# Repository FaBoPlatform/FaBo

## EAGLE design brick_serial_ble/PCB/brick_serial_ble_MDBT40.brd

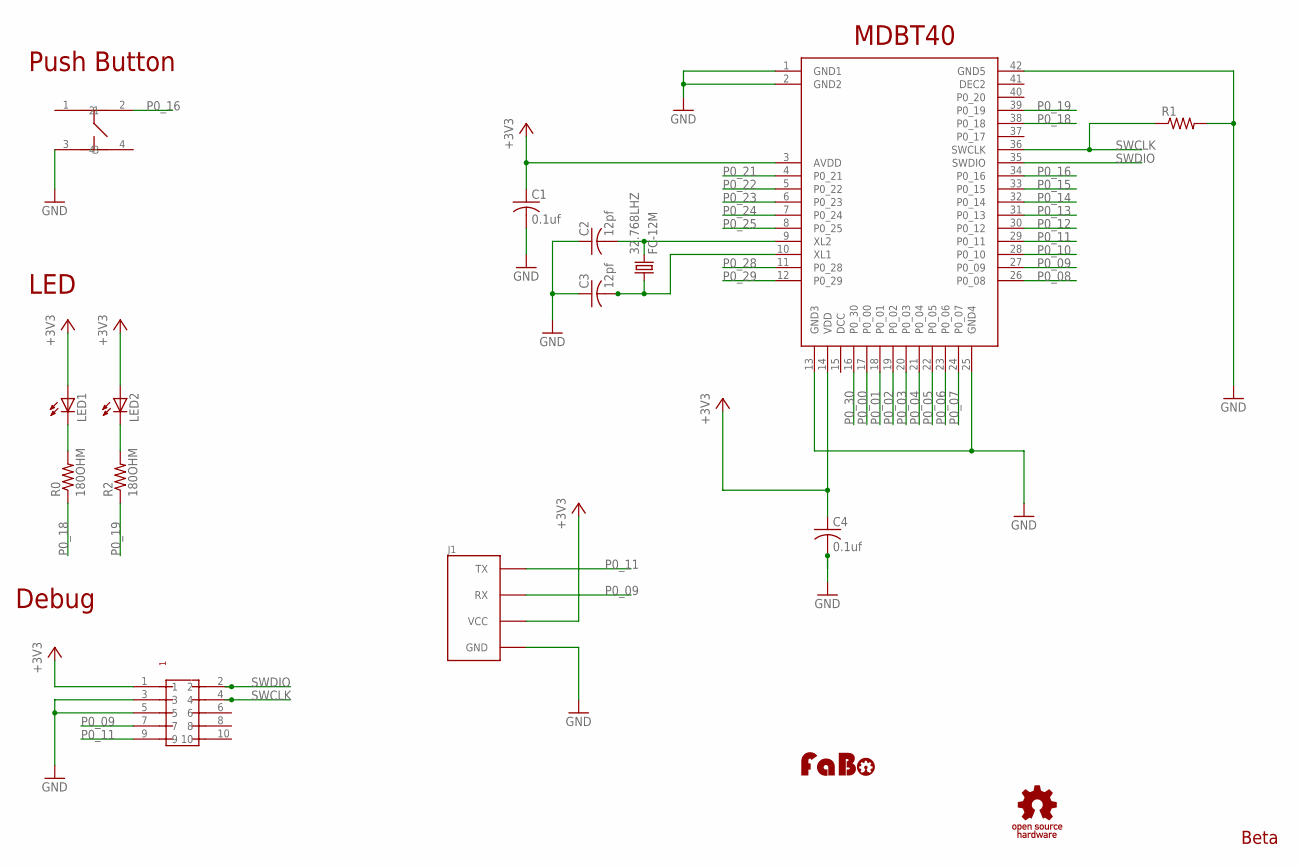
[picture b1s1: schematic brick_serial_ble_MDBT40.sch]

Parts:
32.768LHZ: FC-12M
C1, C4: 0.1uf; C0603
C2, C3: 12pf; C0603
J1: BRICK_SERIAL
LED1, LED2: LEDCHIP-LED0603; CHIP-LED0603
R0, R2: 180OHM; 0603-RES
R1: R-US_R0603; R0603
U$1: RAYTAC-MDBT40
U$2: PIN-HEADER-SMT(1.27MM)2X5
U$3: LOGO_FABO-S; LOGO_FABO_S
U$4: LOGO_OSHW_T-S; LOGO_OSHW_T_S
U$5: SWICTH-4P(KMR2); SWITCH-4P(KMR2)

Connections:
+3V3: C1.1, C4.1, J1.VCC, LED1.A, LED2.A, U$1.3 (AVDD), U$1.14 (VDD), U$2.1
GND: C1.2, C2.1, C3.1, C4.2, J1.GND, R1.2, U$1.1 (GND1), U$1.2 (GND2), U$1.13 (GND3), U$1.25 (GND4), U$1.42 (GND5), U$2.3, U$2.5, U$5.3
LED1: LED1.C, R0.2
unnamed: LED2.C, R2.2
unnamed: 32.768LHZ.2, C2.2, U$1.9 (XL2)
unnamed: 32.768LHZ.1, C3.2, U$1.10 (XL1)
P0_00: U$1.17 (P0_00)
P0_01: U$1.18 (P0_01)
P0_02: U$1.19 (P0_02)
P0_03: U$1.20 (P0_03)
P0_04: U$1.21 (P0_04)
P0_05: U$1.22 (P0_05)
P0_06: U$1.23 (P0_06)
P0_07: U$1.24 (P0_07)
P0_08: U$1.26 (P0_08)
P0_09: J1.RX, U$1.27 (P0_09), U$2.7
P0_10: U$1.28 (P0_10)
P0_11: J1.TX, U$1.29 (P0_11), U$2.9
P0_12: U$1.30 (P0_12)
P0_13: U$1.31 (P0_13)
P0_14: U$1.32 (P0_14)
P0_15: U$1.33 (P0_15)
P0_16: U$1.34 (P0_16), U$5.2
P0_18: R0.1, U$1.38 (P0_18)
P0_19: R2.1, U$1.39 (P0_19)
P0_21: U$1.4 (P0_21)
P0_22: U$1.5 (P0_22)
P0_23: U$1.6 (P0_23)
P0_24: U$1.7 (P0_24)
P0_25: U$1.8 (P0_25)
P0_28: U$1.11 (P0_28)
P0_29: U$1.12 (P0_29)
P0_30: U$1.16 (P0_30)
SWCLK: R1.1, U$1.36 (SWCLK), U$2.4
SWDIO: U$1.35 (SWDIO), U$2.2

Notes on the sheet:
Push Button
Debug
MDBT40
LED
Beta

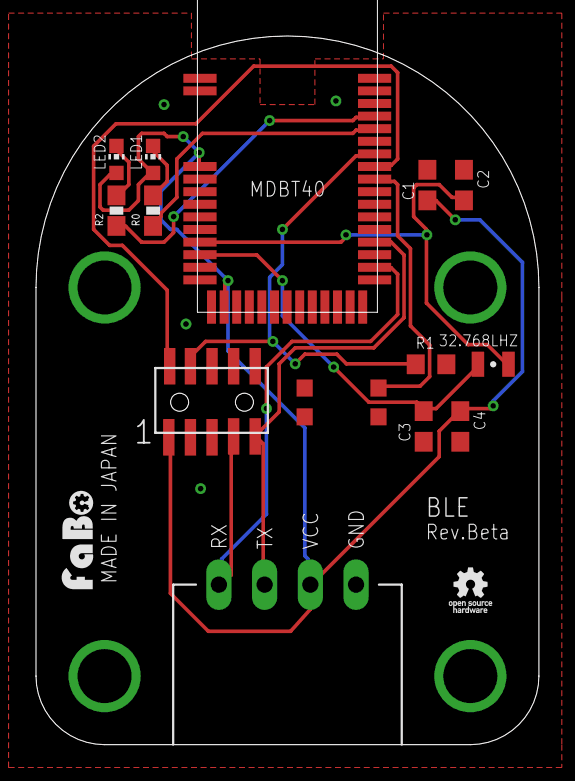
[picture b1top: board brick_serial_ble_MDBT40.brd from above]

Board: 2 copper layers, 27.9 x 39.4 mm, 16 parts (0 on the bottom side), 13 nets.

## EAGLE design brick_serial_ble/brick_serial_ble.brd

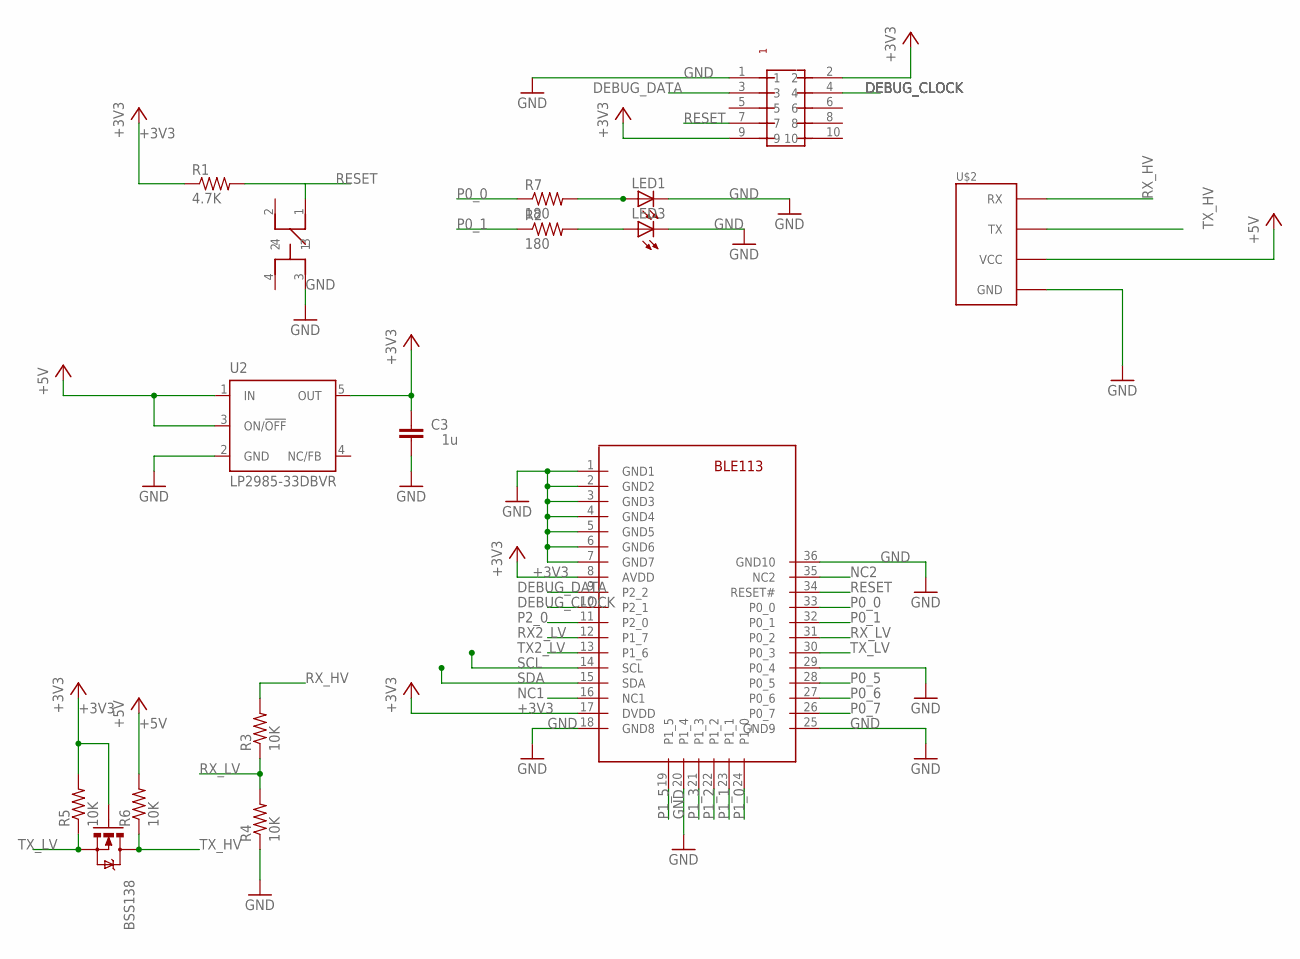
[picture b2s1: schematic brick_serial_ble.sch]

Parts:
BSS138: MOSFET-NCHANNELSMD; SOT23-3
C3: 1u; C0603-ROUND
LED1, LED3: LED_ESML0603; LED_SML0603
R1: 4.7K; 0603-RES
R2, R7: 180; 0603-RES
R3, R4, R5, R6: 10K; 0603-RES
U2: LP2985-33DBVR; SOT23-DBV
U$1: PIN-HEADER-SMT(1.27MM)2X5
U$2: BRICK_SERIAL
U$4: SWITCH-LS6J2M-T; SWICTH-LS6J2M-T
U$6: BLUEGIGA-BLE113

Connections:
+3V3: BSS138.1 (G), C3.2, R1.1, R5.2, U2.5 (OUT), U$1.2, U$1.9, U$6.8 (AVDD), U$6.17 (DVDD)
+5V: R6.2, U2.1 (IN), U2.3 (ON/!OFF), U$2.VCC
DEBUG_CLOCK: U$1.4, U$6.10 (P2_1)
DEBUG_DATA: U$1.3, U$6.9 (P2_2)
GND: C3.1, LED1.C, LED3.C, R4.1, U2.2 (GND), U$1.1, U$2.GND, U$4.3, U$6.1 (GND1), U$6.2 (GND2), U$6.3 (GND3), U$6.4 (GND4), U$6.5 (GND5), U$6.6 (GND6), U$6.7 (GND7), U$6.18 (GND8), U$6.20 (P1_4), U$6.25 (GND9), U$6.29 (P0_4), U$6.36 (GND10)
unnamed: LED1.A, R7.2
unnamed: LED3.A, R2.2
NC1: U$6.16 (NC1)
NC2: U$6.35 (NC2)
P0_0: R7.1, U$6.33 (P0_0)
P0_1: R2.1, U$6.32 (P0_1)
P0_5: U$6.28 (P0_5)
P0_6: U$6.27 (P0_6)
P0_7: U$6.26 (P0_7)
P1_0: U$6.24 (P1_0)
P1_1: U$6.23 (P1_1)
P1_2: U$6.22 (P1_2)
P1_3: U$6.21 (P1_3)
P1_5: U$6.19 (P1_5)
P2_0: U$6.11 (P2_0)
RESET: R1.2, U$1.7, U$4.1, U$6.34 (RESET#)
RX2_LV: U$6.12 (P1_7)
RX_HV: R3.2, U$2.RX
RX_LV: R3.1, R4.2, U$6.31 (P0_2)
SCL: U$6.14 (SCL)
SDA: U$6.15 (SDA)
TX2_LV: U$6.13 (P1_6)
TX_HV: BSS138.3 (D), R6.1, U$2.TX
TX_LV: BSS138.2 (S), R5.1, U$6.30 (P0_3)

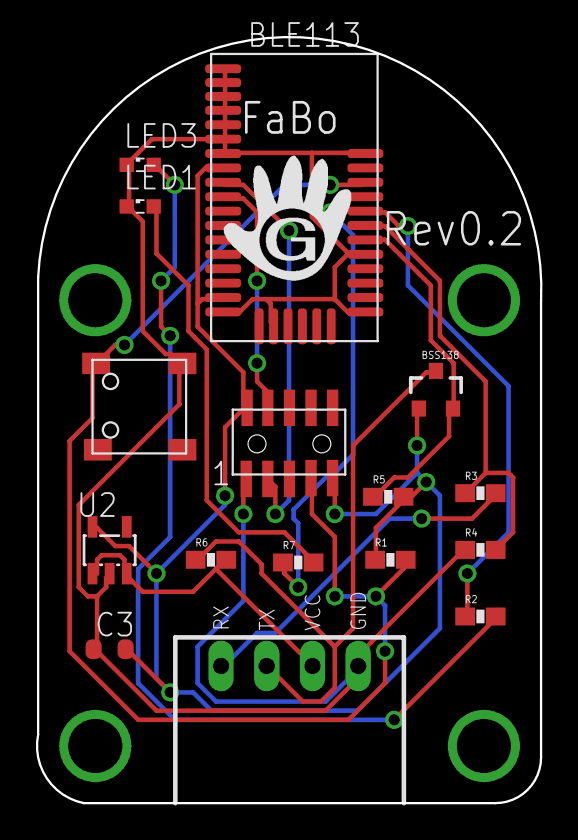
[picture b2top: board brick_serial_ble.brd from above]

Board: 2 copper layers, 28.0 x 42.6 mm, 16 parts (0 on the bottom side), 14 nets.

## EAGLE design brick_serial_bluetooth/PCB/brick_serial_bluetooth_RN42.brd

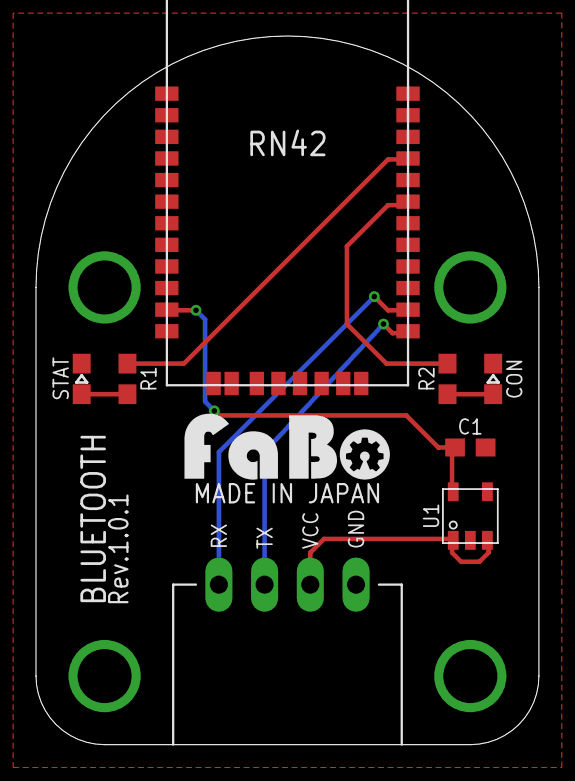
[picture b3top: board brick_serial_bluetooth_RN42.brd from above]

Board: 2 copper layers, 27.9 x 39.4 mm, 10 parts (0 on the bottom side), 9 nets.

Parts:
C1: 1uF; EIA0603
CON: EIA0603-LED
J1: FABO_BRICK_SERIAL
R1, R2: 220; EIA0603
STAT: EIA0603-LED
U1: SOT_23_5
U$1: MICROCHIP-RN42
U$3: LOGO_FABO_M
U$4: LOGO_OSHW_T_M_BOTTOM

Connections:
3V3: C1.1, U1.5, U$1.11
GND: C1.2, CON.C, J1.GND, STAT.C, U1.2, U$1.1, U$1.4, U$1.12, U$1.28, U$1.29
unnamed: R1.1, STAT.A
unnamed: R2.2, U$1.19
unnamed: R1.2, U$1.21
unnamed: CON.A, R2.1
unnamed: J1.VCC, U1.1, U1.3
RX: J1.RX, U$1.14
TX: J1.TX, U$1.13

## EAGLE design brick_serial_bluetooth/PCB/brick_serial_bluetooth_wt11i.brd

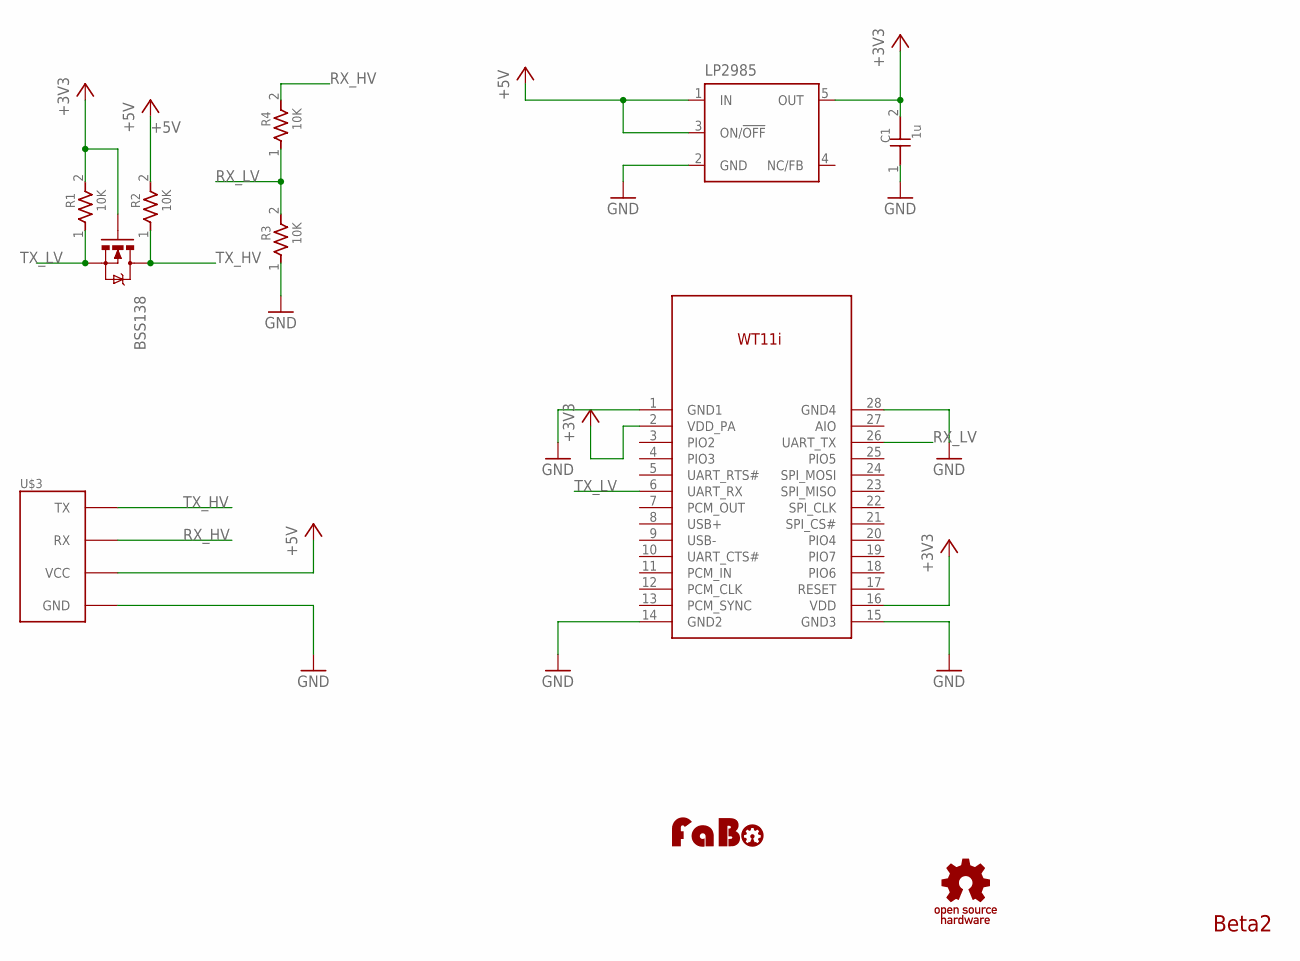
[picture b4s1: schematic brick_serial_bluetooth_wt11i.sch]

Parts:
BSS138: MOSFET-NCHANNELSMD; SOT23-3
C1: 1u; 0603
LP2985: LP2985-XXDBVR33; SOT23-DBV
R1, R2, R3, R4: 10K; 0603
U$1: BLUEGIGA-WT11I
U$3: BRICK_SERIAL
U$4: LOGO_OSHW_T-S; LOGO_OSHW_T_S
U$5: LOGO_FABO-S; LOGO_FABO_S

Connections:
+3V3: BSS138.1 (G), C1.2, LP2985.5 (OUT), R1.2, U$1.2 (VDD_PA), U$1.16 (VDD)
+5V: LP2985.1 (IN), LP2985.3 (ON/!OFF), R2.2, U$3.VCC
GND: C1.1, LP2985.2 (GND), R3.1, U$1.1 (GND1), U$1.14 (GND2), U$1.15 (GND3), U$1.28 (GND4), U$3.GND
RX_HV: R4.2, U$3.RX
RX_LV: R3.2, R4.1, U$1.26 (UART_TX)
TX_HV: BSS138.3 (D), R2.1, U$3.TX
TX_LV: BSS138.2 (S), R1.1, U$1.6 (UART_RX)

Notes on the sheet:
Beta2

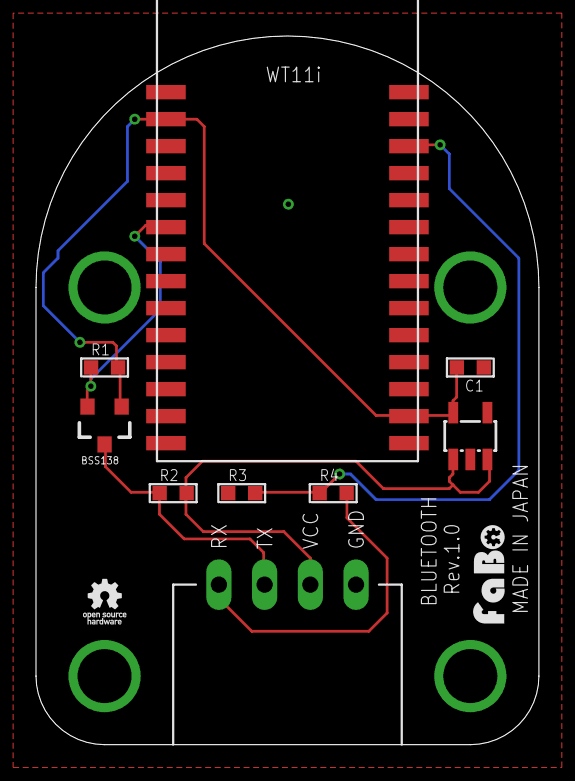
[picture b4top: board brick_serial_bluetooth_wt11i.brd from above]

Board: 2 copper layers, 27.9 x 39.4 mm, 11 parts (0 on the bottom side), 7 nets.

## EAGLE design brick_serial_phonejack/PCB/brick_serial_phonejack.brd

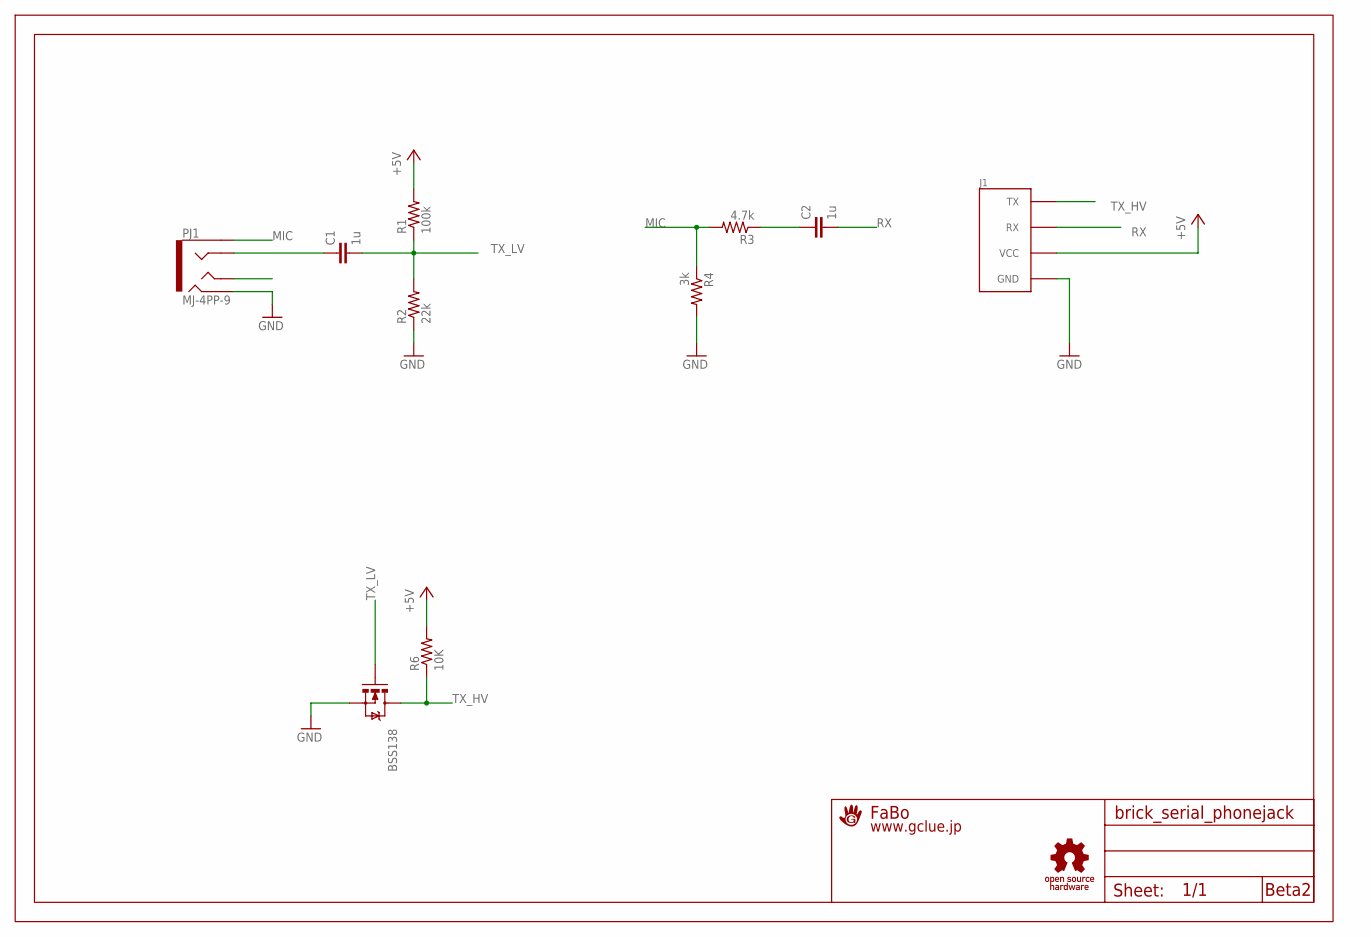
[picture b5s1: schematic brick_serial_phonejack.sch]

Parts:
BSS138: MOSFET-NCHANNELSMD; SOT23-3
C1, C2: 1u; EIA0603-CAP
J1: 0; BRICK_SERIAL
PJ1: MJ-4PP-9; PHONEJACK-MJ-4PP-9
R1: 100k; EIA0603-RES
R2: 22k; EIA0603-RES
R3: 4.7k; EIA0603-RES
R4: 3k; EIA0603-RES
R6: 10K; 0603-RES
U$2: LOGO_OSHW_T-S; LOGO_OSHW_T_S
U$5: A4L-LOC-FABO_S; LOGO_FABO_S

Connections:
+5V: J1.VCC, R1.2, R6.2
GND: BSS138.2 (S), J1.GND, PJ1.B, R2.1, R4.2
MIC: PJ1.A, R3.2, R4.1
unnamed: C2.1, R3.1
unnamed: C1.1, PJ1.C
RX: C2.2, J1.RX
TX_HV: BSS138.3 (D), J1.TX, R6.1
TX_LV: BSS138.1 (G), C1.2, R1.1, R2.2

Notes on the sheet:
Beta2

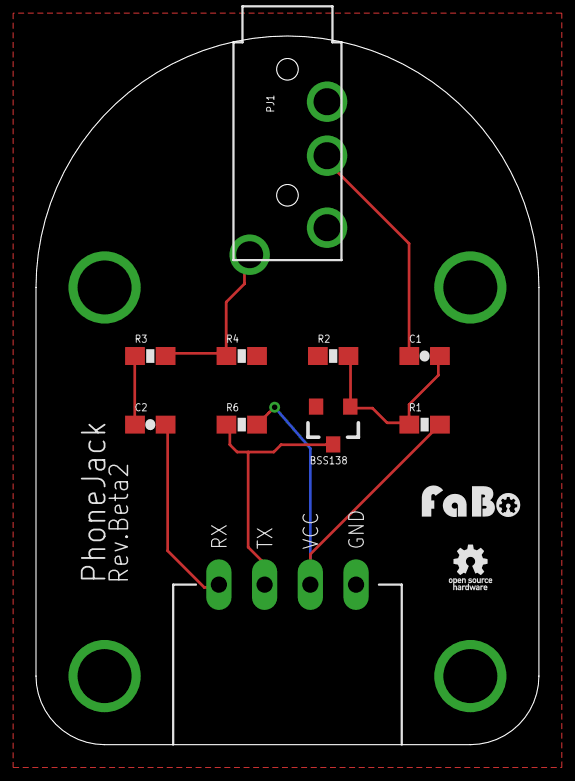
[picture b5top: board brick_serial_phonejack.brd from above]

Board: 2 copper layers, 27.9 x 39.4 mm, 12 parts (0 on the bottom side), 8 nets.

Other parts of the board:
U$1: LOGO_FABO_S

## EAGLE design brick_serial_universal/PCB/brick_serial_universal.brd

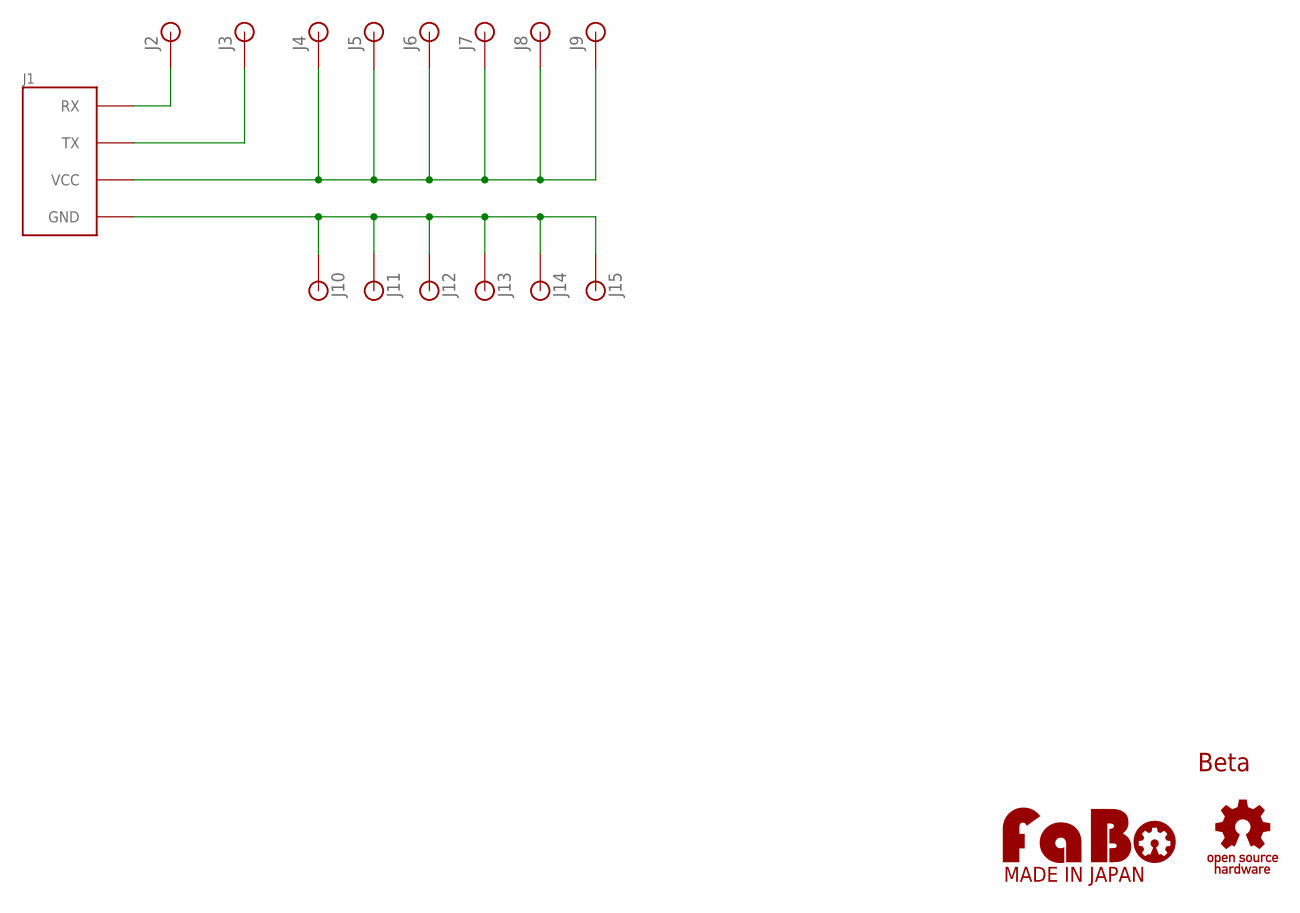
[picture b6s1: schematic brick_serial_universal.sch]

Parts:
J1: FABO_BRICK_SERIAL-UNIVERSAL; FABO_BRICK_SERIAL_UNIVERSAL
J2, J3, J4, J5, J6, J7, J8, J9, J10, J11, J12, J13, J14, J15: PINHEAD_1X1-NONAME; PIN_1X1_NONAME
U$2: LOGO_OSHW-S_BOTTOM; LOGO_OSHW_S_BOTTOM
U$3: LOGO_FABO-M_BOTTOM; LOGO_FABO_M_BOTTOM

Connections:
GND: J1.GND, J10.1, J11.1, J12.1, J13.1, J14.1, J15.1
RX: J1.RX, J2.1
TX: J1.TX, J3.1
VCC: J1.VCC, J4.1, J5.1, J6.1, J7.1, J8.1, J9.1

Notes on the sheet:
Beta

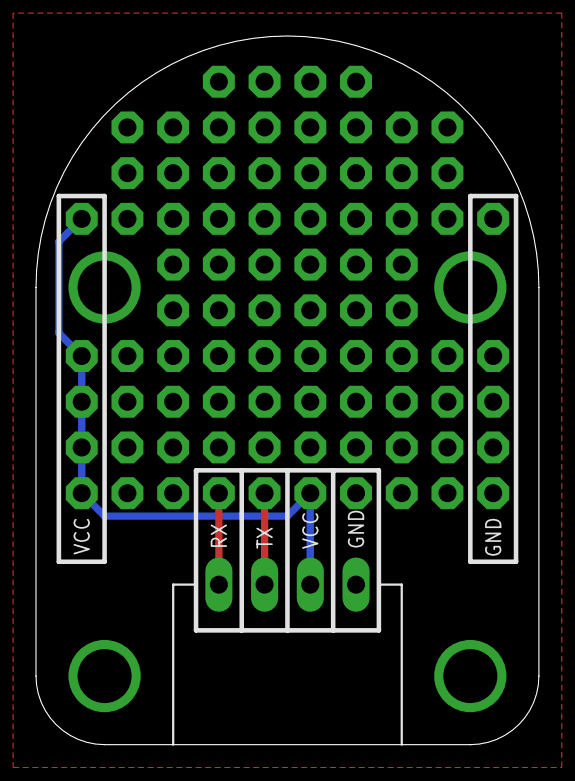
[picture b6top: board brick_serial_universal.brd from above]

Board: 2 copper layers, 27.9 x 39.4 mm, 17 parts (0 on the bottom side), 4 nets.

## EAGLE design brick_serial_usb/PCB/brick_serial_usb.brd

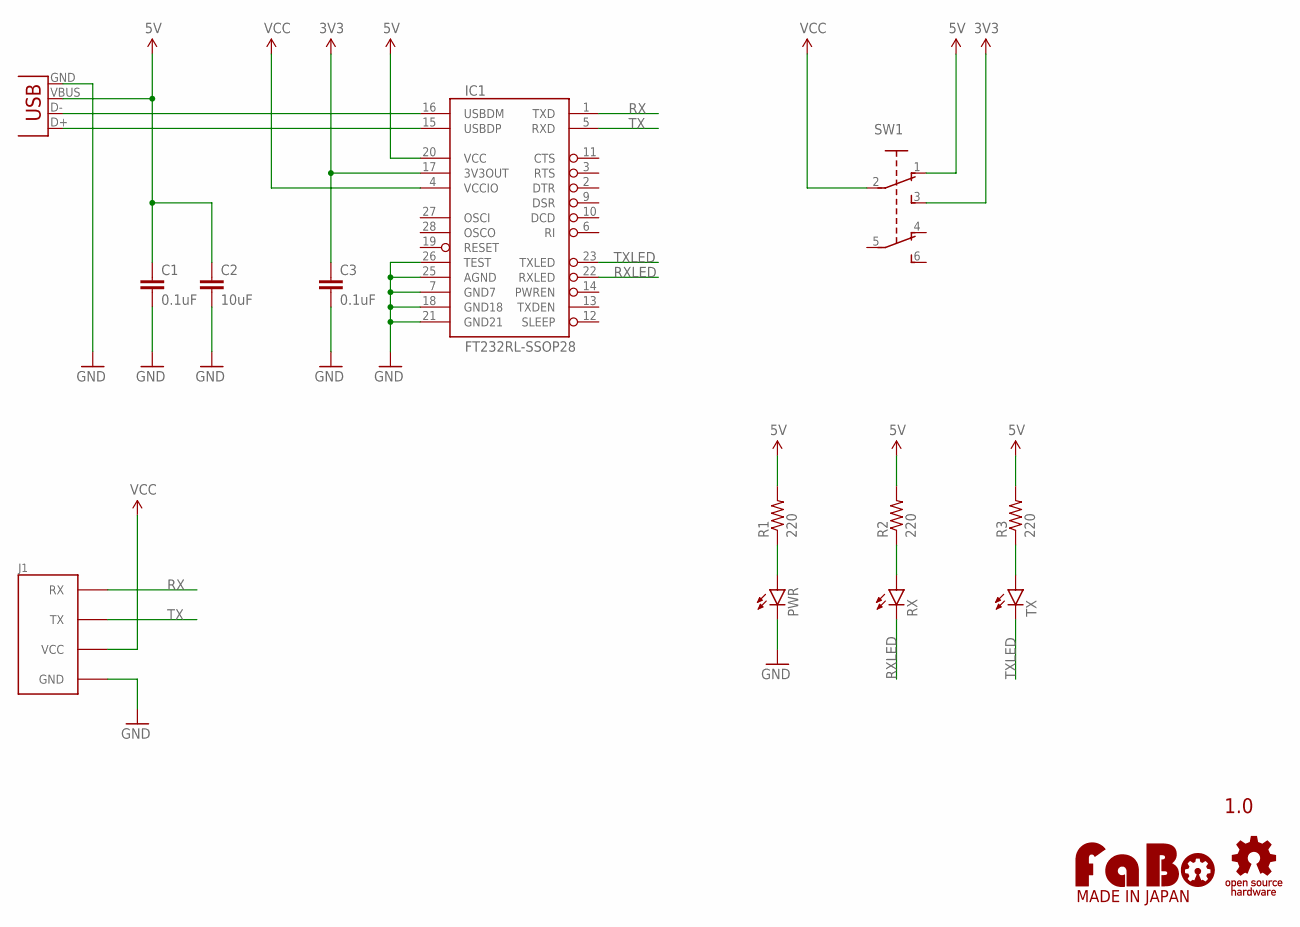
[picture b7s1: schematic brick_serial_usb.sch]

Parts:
C1, C3: 0.1uF; EIA0603
C2: 10uF; EIA0603
IC1: FT232RL-SSOP28; SSOP28
J1: FABO_BRICK_SERIAL
JP1: USB-B-MICRO_SMD; USB_B_MICRO
PWR: LED-EIA0603; EIA0603-LED
R1, R2, R3: 220; EIA0603
RX: LED-EIA0603; EIA0603-LED
SW1: SWITCH-SLIDE_2C2P-JS202011SCQN; C&K_JS202011SCQN
TX: LED-EIA0603; EIA0603-LED
U$5: LOGO_OSHW-T_M_BOTTOM; LOGO_OSHW_T_M_BOTTOM
U$6: LOGO_FABO-M; LOGO_FABO_M

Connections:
3V3: C3.1, IC1.17 (3V3OUT), SW1.3
5V: C1.1, C2.1, IC1.20 (VCC), JP1.VBUS, R1.2, R2.2, R3.2, SW1.1
GND: C1.2, C2.2, C3.2, IC1.7 (GND7), IC1.18 (GND18), IC1.21 (GND21), IC1.25 (AGND), IC1.26 (TEST), J1.GND, JP1.GND, PWR.C
unnamed: PWR.A, R1.1
unnamed: R3.1, TX.A
unnamed: R2.1, RX.A
RX: IC1.1 (TXD), J1.RX
RXLED: IC1.22 (RXLED), RX.C
TX: IC1.5 (RXD), J1.TX
TXLED: IC1.23 (TXLED), TX.C
USBDM: IC1.16 (USBDM), JP1.D-
USBDP: IC1.15 (USBDP), JP1.D+
VCC: IC1.4 (VCCIO), J1.VCC, SW1.2

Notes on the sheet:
1.0

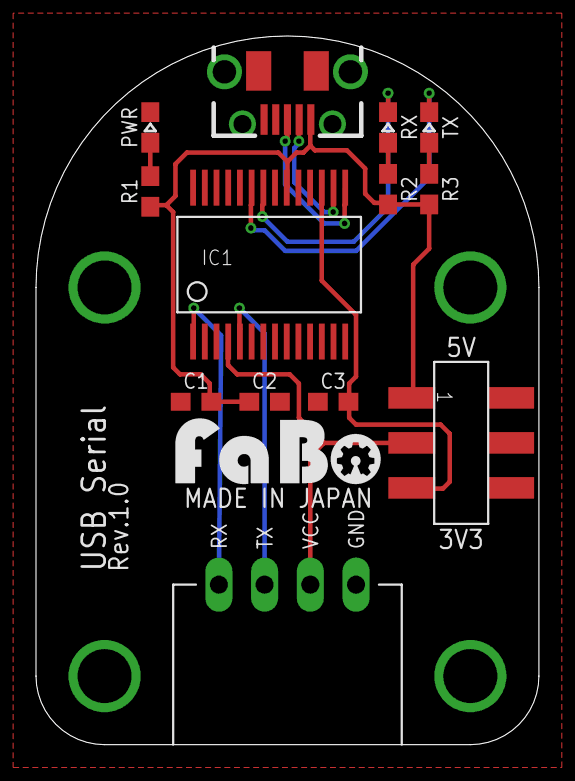
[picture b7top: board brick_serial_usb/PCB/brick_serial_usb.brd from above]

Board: 2 copper layers, 27.9 x 39.4 mm, 15 parts (0 on the bottom side), 13 nets.

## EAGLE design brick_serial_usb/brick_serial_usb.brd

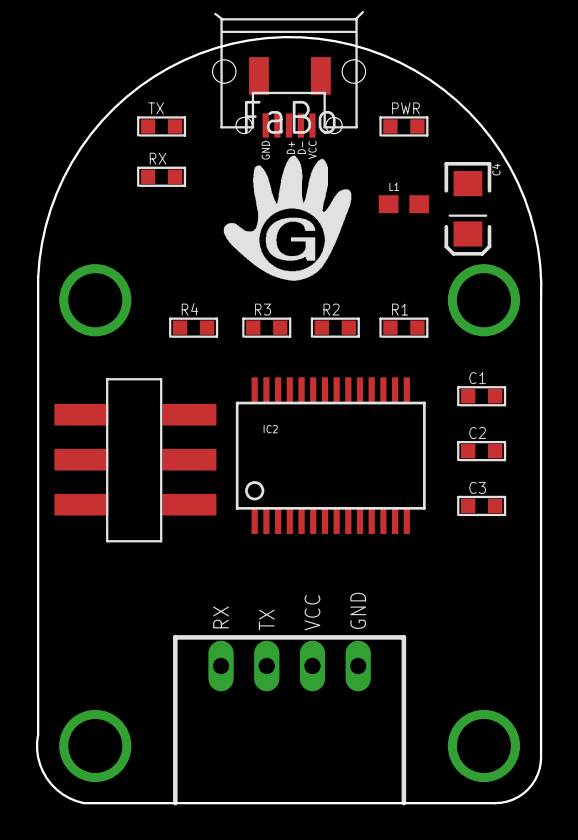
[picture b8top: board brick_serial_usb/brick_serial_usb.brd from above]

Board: 2 copper layers, 28.0 x 42.6 mm, 16 parts (0 on the bottom side), 15 nets, no tracks yet.

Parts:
C1: 10uf; 0603
C2, C3: 0.1uf; 0603
C4: 10μF; EIA3216
IC2: FT232RLSSOP; SSOP28DB
L1: 0603
PWR: LED0603; 0603
R1, R2, R3: 270; 0603
R4: 4.7K; 0603
RX: LED0603; 0603
TX: LED0603; 0603
U$1: USB-MICRO-B-FEMALE
U$2: C&K_JS202011SCQN
U$3: BRICK_SERIAL

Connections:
+3V3: C2.2, IC2.17, U$2.3
+5V: C3.2, C4.A, IC2.4, IC2.20, L1.2, U$2.1
D+: IC2.15, U$1.D+
D-: IC2.16, U$1.D-
GND: C1.1, C2.1, C3.1, C4.C, IC2.7, IC2.18, IC2.21, IC2.25, IC2.26, PWR.CATHODE, U$1.GND, U$1.GND1, U$1.GND2, U$3.GND
unnamed: C1.2, L1.1, U$1.VCC
unnamed: R1.1, TX.ANODE
unnamed: R2.1, RX.ANODE
unnamed: PWR.ANODE, R3.1
RESET: IC2.19, R4.1
RX: IC2.5, U$3.RX
RXLED: IC2.22, RX.CATHODE
TX: IC2.1, U$3.TX
TXLED: IC2.23, TX.CATHODE
VCC: R1.2, R2.2, R3.2, R4.2, U$2.5, U$3.VCC

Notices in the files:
parts and their libraries:
SparkFun: Licensing: CC v3.0 Share-Alike You are welcome to use this library for commercial purposes.
FaBo-Template: Released under the Creative Commons Attribution-ShareAlike 4.0 License
https://creativecommons.org/licenses/by-sa/4.0
FaBo-etc: Released under the Creative Commons
